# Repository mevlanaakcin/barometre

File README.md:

# barometre
Basınç Ölçmeyi amaçlayan bir çalışma

<h3>PCB Tasarımı</h3><br>
Elektronik devre şeması ve PCB board tasarımı Eagle de tasarlandı.<br>

<br>
0-20 mbar basınç/vakum ve 0-12bar basınç ölçme kabiliyetine sahip ölçü aletidir.<br>
MPXV7002DP CASE 1351 Basınç sensörü Kullanıldı.

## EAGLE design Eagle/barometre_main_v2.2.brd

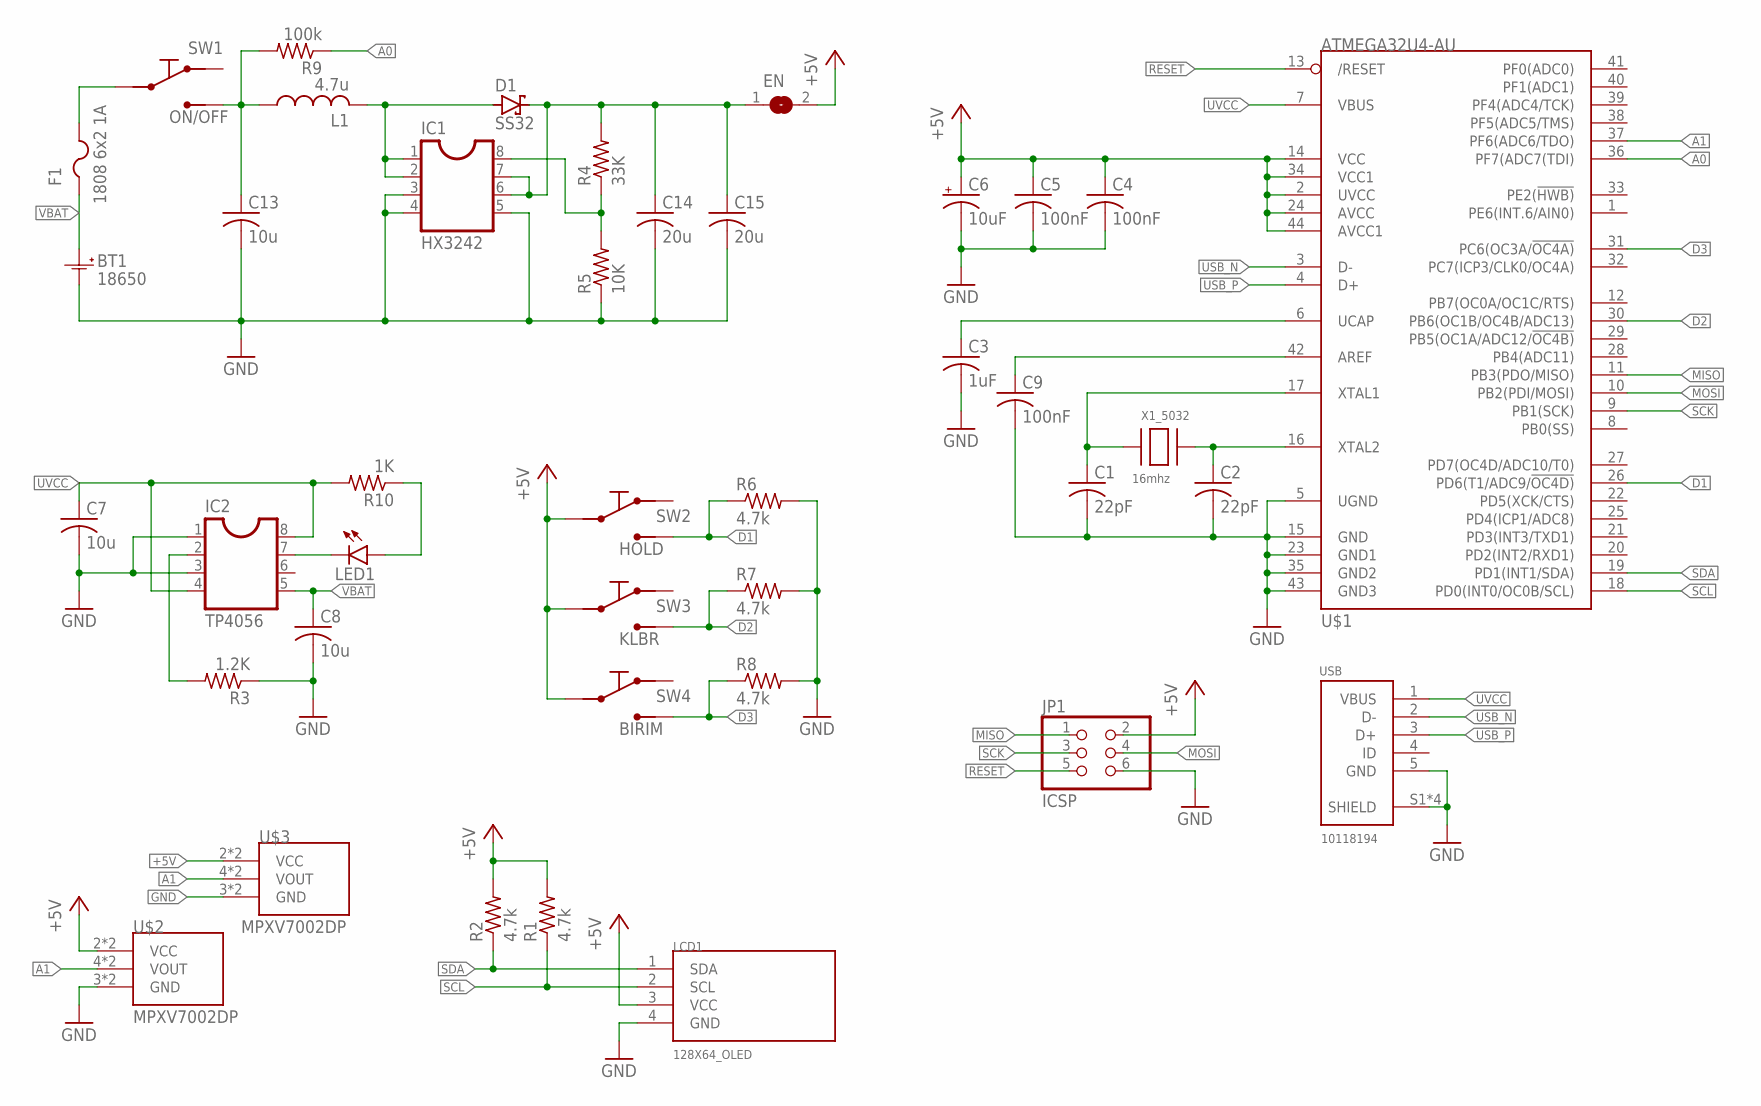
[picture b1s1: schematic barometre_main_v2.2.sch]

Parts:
BT1: 18650; 18650_PCB
C1, C2: 22pF; C0805
C3: 1uF; C0805
C4, C5, C9: 100nF; C0805
C6: 10uF; SMC_B
C7, C8, C13: 10u; C0805
C14, C15: 20u; C0805
D1: SS32; SMC
EN: SJ
F1: 1808 6x2 1A; 1812
IC1: HX3242; SO-8
IC2: TP4056; SO-8
JP1: ICSP; 2X03
L1: 4.7u; L5650M
LCD1: 128X64_OLED
LED1: LEDCHIPLED_0805; CHIPLED_0805
R1, R2, R6, R7, R8: 4.7k; R0805
R3: 1.2K; R0805
R4: 33K; R0805
R5: 10K; R0805
R9: 100k; R0805
R10: 1K; R0805
SW1: ON/OFF; BUTTON_6_PIN
SW2: HOLD; BUTTON_6_PIN
SW3: KLBR; BUTTON_6_PIN
SW4: BIRIM; BUTTON_6_PIN
U$1: ATMEGA32U4-AU; TQFP44
U$2, U$3: MPXV7002DP
USB: 10118194
X1_5032: 16mhz; NX5032

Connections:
+5V: C4.1, C5.1, C6.+, EN.2, JP1.2, LCD1.3 (VCC), R1.2, R2.2, SW2.P$2, SW2.P$5, SW3.P$2, SW3.P$5, SW4.P$2, SW4.P$5, U$1.2 (UVCC), U$1.14 (VCC), U$1.24 (AVCC), U$1.34 (VCC1), U$1.44 (AVCC1), U$2.2 (VCC), U$2.P$2 (VCC), U$3.2 (VCC), U$3.P$2 (VCC)
A0: R9.1, U$1.36 (PF7(ADC7(TDI))
A1: U$1.37 (PF6(ADC6/TDO)), U$2.4 (VOUT), U$2.P$4 (VOUT), U$3.4 (VOUT), U$3.P$4 (VOUT)
D1: R6.1, SW2.P$1, SW2.P$6, U$1.26 (PD6(T1/ADC9/!OC4D))
D2: R7.1, SW3.P$1, SW3.P$6, U$1.30 (PB6(OC1B/OC4B/ADC13))
D3: R8.1, SW4.P$1, SW4.P$6, U$1.31 (PC6(OC3A/!OC4A))
GND: BT1.N, C1.2, C2.2, C3.2, C4.2, C5.2, C6.-, C7.2, C8.2, C9.2, C13.2, C14.2, C15.2, IC1.3, IC1.4, IC1.5, IC2.1, IC2.3, JP1.6, LCD1.4 (GND), R3.1, R5.1, R6.2, R7.2, R8.2, U$1.5 (UGND), U$1.15 (GND), U$1.23 (GND1), U$1.35 (GND2), U$1.43 (GND3), U$2.3 (GND), U$2.P$3 (GND), U$3.3 (GND), U$3.P$3 (GND), USB.5 (GND), USB.S1 (SHIELD), USB.S2 (SHIELD), USB.S3 (SHIELD), USB.S6 (SHIELD)
MISO: JP1.1, U$1.11 (PB3(PDO/MISO))
MOSI: JP1.4, U$1.10 (PB2(PDI/MOSI))
unnamed: IC2.2, R3.2
unnamed: C3.1, U$1.6 (UCAP)
unnamed: C1.1, U$1.17 (XTAL1), X1_5032.P$1
unnamed: C2.1, U$1.16 (XTAL2), X1_5032.P$2
unnamed: LED1.A, R10.1
unnamed: F1.2, SW1.P$2, SW1.P$5
unnamed: D1.A, IC1.1, IC1.2, L1.2
unnamed: C13.1, L1.1, R9.2, SW1.P$1, SW1.P$6
unnamed: IC2.7, LED1.C
unnamed: C9.1, U$1.42 (AREF)
unnamed: IC1.8, R4.1, R5.2
unnamed: C14.1, C15.1, D1.C, EN.1, IC1.6, IC1.7, R4.2
RESET: JP1.5, U$1.13 (/RESET)
SCK: JP1.3, U$1.9 (PB1(SCK))
SCL: LCD1.2 (SCL), R1.1, U$1.18 (PD0(INT0/OC0B/SCL))
SDA: LCD1.1 (SDA), R2.1, U$1.19 (PD1(INT1/SDA))
USB_N: U$1.3 (D-), USB.2 (D-)
USB_P: U$1.4 (D+), USB.3 (D+)
UVCC: C7.1, IC2.4, IC2.8, R10.2, U$1.7 (VBUS), USB.1 (VBUS)
VBAT: BT1.P, C8.1, F1.1, IC2.5

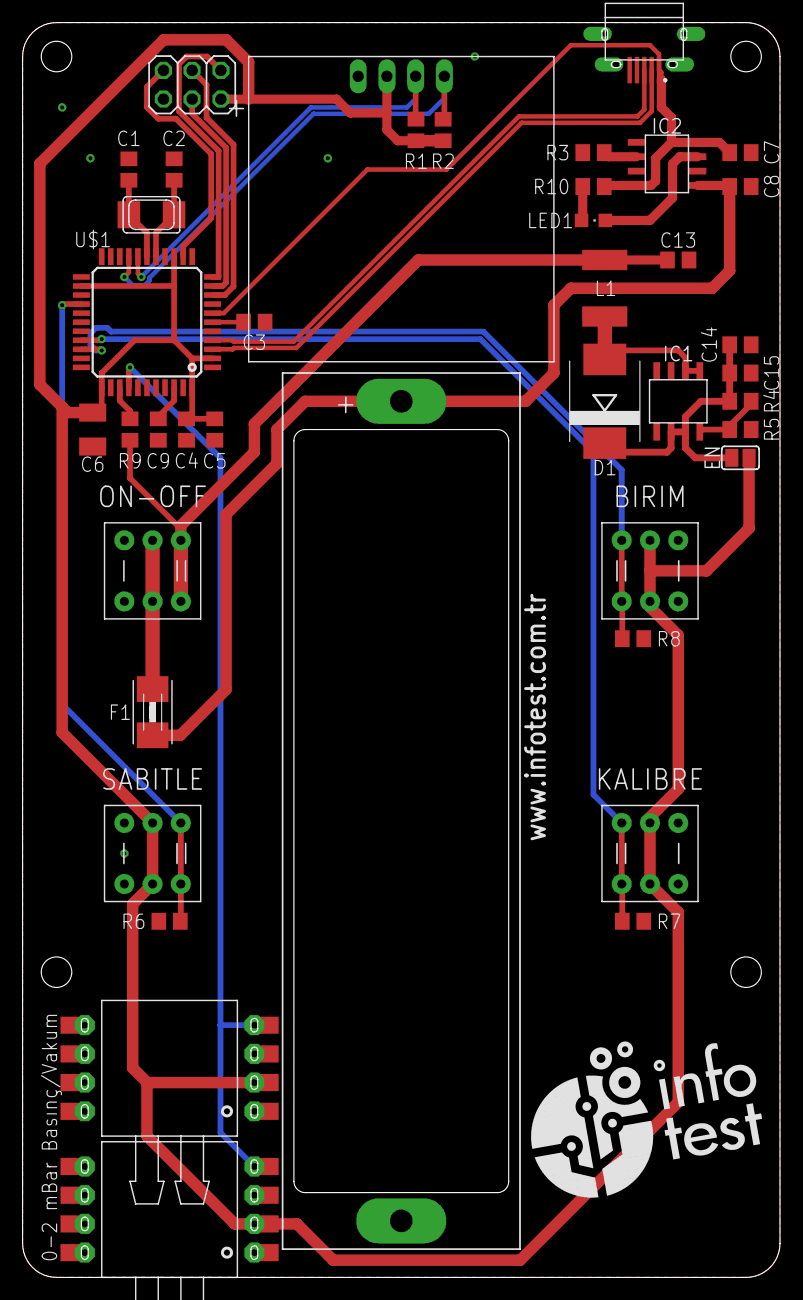
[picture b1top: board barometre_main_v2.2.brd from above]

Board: 2 copper layers, 67.0 x 111.0 mm, 41 parts (0 on the bottom side), 29 nets.
